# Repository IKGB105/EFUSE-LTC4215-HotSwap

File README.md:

# Hot-Swap eFuse (LTC4215)

12 V hot-swap / electronic-fuse front-end built around the LTC4215 hot-swap controller, documented as an
honest engineering logbook: every result is marked as calculated, simulated, or pending — no invented
placeholders. A deliberately small, fast project in the same series as
[LM317-Adjustable-PowerSupply](https://github.com/IKGB105/LM317-Adjustable-PowerSupply) and the LM2596/VRM
projects — chosen to add a self-contained portfolio result without derailing the in-progress 2-phase VRM
work, while staying on-theme for a server/GPU power-delivery specialization (live board insertion, inrush
limiting, and electronic circuit breaking).

- **Input:** 12 V DC
- **Circuit breaker trip:** 5 A (fast, non-resettable — latches off, no auto-retry)
- **Steady-state current limit (electrical):** 15 A (post-startup foldback release)
- **UV/OV lockout:** ~10.6 V / ~14.3 V (auto-retry on both)

> ⚠️ **15 A continuous is not thermally safe in still air on this layout.** A coupled electrical-thermal
> COMSOL model (current flow in the copper solved together with the heat) found the copper pours
> themselves dissipate 1.6 W — as much as every component combined — pushing the sense resistor (R5) to
> 170 °C and the MOSFET junction to its 150 °C limit at 15 A with convection only. **12.5 A continuous is
> comfortable** (128 °C / 113 °C). See [Thermal FEM](#thermal-fem-comsol) below.

> ⚠️ **Simulation + PCB layout only, not built.** Confirmed as the project scope from the start (same as
> `VRM_2PHASE_LTC1929`). The schematic and PCB are complete and ERC/DRC-clean but have not been sent to
> fabrication.

<table>
<tr>
<td><br><sub>KiCad — schematic</sub></td>
<td><br><sub>KiCad — PCB 3D render</sub></td>
<td><br><sub>COMSOL — thermal result (12 V, 15 A, R5/Q1 close-up)</sub></td>
</tr>
</table>

## Key results (simulated, verified from the LTspice `.raw` file)

- **Controlled startup:** inrush current peaks at **5.2 A**, landing almost exactly on the calculated 5 A
  circuit-breaker target — confirms the soft-start (SS) ramp and $R_{SENSE}$ are sized consistently with
  the breaker threshold. $V_{OUT}$ reaches 12 V in ≈51 ms.
- **Automatic UV recovery:** a 12 V → 8 V dip triggers a fast (~300 µs) output sag (the MOSFET's body
  diode conducting, not active protection), then a full, unattended recovery — but only ~106–112 ms after
  $V_{DD}$ returns, because the LTC4215's internal startup-sequencer delay re-arms on every restart, not
  just the first power-up.
- **Permanent latch-off on a hard short:** the circuit breaker trips within the datasheet's 20 µs filter
  and the output stays at 0 V for the rest of the run — no auto-retry, by design (`ocautoretry=0`).

Two non-obvious simulation pitfalls (a flat-DC source masking the entire power-up transient, and the
100 ms internal startup delay looking like a dead circuit) are documented in the report so they aren't
re-discovered from scratch on a future project using this IC family.

## Repository structure

```
docs/         LaTeX report (efuse_ltc4215.tex) + the LTC4215 datasheet
kicad/        KiCad project — schematic + PCB, ERC/DRC clean
simulation/   LTspice schematic (EFuse.asc) — startup, UV auto-retry, and OC fault tests
fem/          COMSOL thermal FEM — script-generated model, results CSVs, figures
```

## Document

The full report (controller selection, datasheet review, component derivations, LTspice simulation
methodology and results, PCB layout decisions, debugging pitfalls found along the way) is in
[`docs/efuse_ltc4215.pdf`](docs/efuse_ltc4215.pdf) — compiled and committed. Source is
[`docs/efuse_ltc4215.tex`](docs/efuse_ltc4215.tex) if you want to edit or recompile it yourself
(`pdflatex`).

## Design

Topology and component values are adapted directly from the LTC4215 datasheet's own validated reference
circuit ("12V Application with 5A Circuit Breaker," Figure 1) — every UV/OV/FB threshold is independently
re-derived and numerically cross-checked against the datasheet's comparator thresholds, not copied
blindly. Full derivation, equations, and a discussion of the one component substitution needed for
simulation (TVS: BZX84C15L in place of the real BOM's P6KE16A, no local SPICE model for the latter) are in
the report.

## SPICE Simulation (LTspice)

In [`simulation/`](simulation/) — three scenarios validated against the `.raw` file: controlled startup
(soft-start ramp, inrush current), an undervoltage fault with automatic recovery, and a hard output short
with permanent latch-off. See the report for full waveform data and the two IC-specific debugging
pitfalls found along the way.

## PCB (KiCad)

In [`kicad/EFUSE/`](kicad/EFUSE/) — ERC and DRC both clean. Two-layer board (single ground domain, 15 A
doesn't justify more layers). Notable layout decisions, documented in full in the report:

- QFN-24 package required (not the smaller SSOP-16) because this design uses the OV protection pin, which
  the SSOP-16 doesn't expose.
- Kelvin connection at the current-sense resistor ($R_{SENSE}$, 2512 package): SENSE− routed as a
  dedicated low-current tap directly off the sense resistor's own pad, not off the high-current trace
  toward the MOSFET.
- Dedicated +12 V and SOURCE/$V_{OUT}$ copper pours (not just traces), sized for the 15 A steady-state
  current per IPC-2221; solid GND pour on the bottom layer with via-stitching (not via-in-pad, to avoid a
  solder-wicking risk) under the IC's exposed pad.
- All-SMD assembly except where physically impossible: the TVS (DO-15, no SMD option at 600 W peak pulse
  power), the 12 mF output capacitor (no ceramic SMD exists at that value), and the input/output
  connectors (AMASS XT60).

## Thermal FEM (COMSOL)

In [`fem/`](fem/) — *Heat Transfer in Solids*, natural convection, 25 °C ambient, no heatsink, at the
continuous 12 V/15 A operating point. Unlike the LM317/LM2596 projects, the current flow through the
copper pours is solved together with the heat (an *Electric Currents, Shell* model coupled both ways to
the thermal one), not neglected — this is what surfaced the 1.6 W of copper $I^2R$ loss that the earlier
hand estimate (≈0.9 W) missed by almost 2×. The whole model is built from a script
([`fem/codigo/termico_efuse.py`](fem/codigo/termico_efuse.py)) that reads vias directly from the
`.kicad_pcb`, so it regenerates if the board changes.

**Key findings:**
- The sense resistor (R5), not the MOSFET, is the hottest part — same pattern as the LM2596 project, where
  the catch diode (not the regulator IC) turned out to be the real limit.
- Thermal vias added under R5/Q1 (stitched to a dedicated SENSE− copper island cut out of the ground pour
  — they can't go straight to GND without shorting) lower both by ≈10 °C, but the bigger issue is the total
  heat on a small board, not just how it escapes R5/Q1.
- 15 A continuous: R5 at 170 °C, Q1's junction at its 150 °C rated limit (convection only). With radiation
  (realistic for a solder-masked board): 112–124 °C on Q1, 133–141 °C on R5 — within limits but little
  margin.
- To reach 15 A continuous safely: 2 oz copper (halves the pour loss), wider/shorter pours, a
  higher-rated metal-strip R5, or airflow — documented as pending, not implemented.

## License

MIT — see [LICENSE](LICENSE).

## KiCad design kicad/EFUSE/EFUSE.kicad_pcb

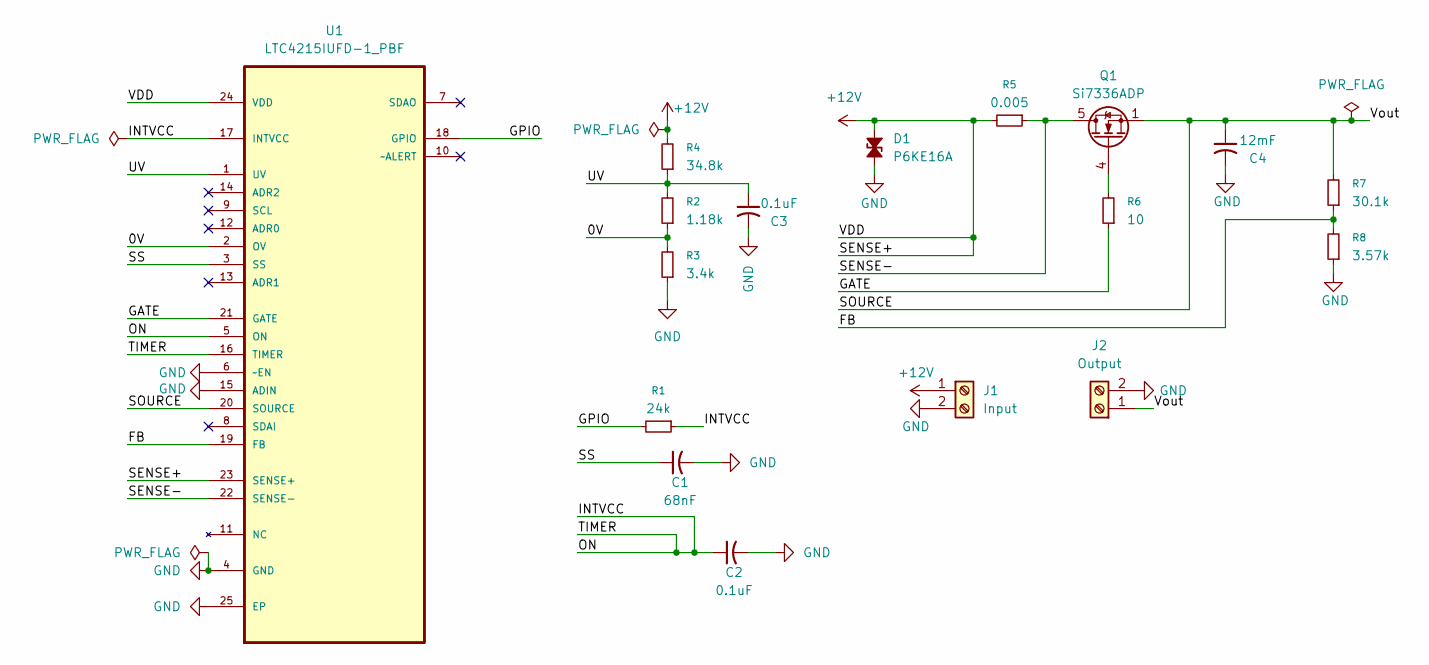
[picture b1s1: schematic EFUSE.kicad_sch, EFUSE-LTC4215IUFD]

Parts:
C1: 68nF; C_0805_2012Metric
C2, C3: 0.1uF; C_0805_2012Metric
C4: 12mF; CP_Radial_D16.0mm_P7.50mm
D1: P6KE16A; D_DO-15_P10.16mm_Horizontal
J1: Input; AMASS_XT60-M_1x02_P7.20mm_Vertical
J2: Output; AMASS_XT60-M_1x02_P7.20mm_Vertical
Q1: Si7336ADP; PowerPAK_SO-8_Single
R1: 24k; R_0805_2012Metric
R2: 1.18k; R_0805_2012Metric
R3: 3.4k; R_0805_2012Metric
R4: 34.8k; R_0805_2012Metric
R5: 0.005; R_2512_6332Metric
R6: 10; R_0805_2012Metric
R7: 30.1k; R_0805_2012Metric
R8: 3.57k; R_0805_2012Metric
U1: LTC4215IUFD-1_PBF; QFN50P400X500X80-25N; MPN LTC4215IUFD-2#TRPBF; DigiKey_Part_Number LTC4215IUFD-1#PBF-ND

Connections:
+12V: D1.1 (A1), J1.1, R4.2, R5.2, U1.23 (SENSE+), U1.24 (VDD)
/0V: R2.1, R3.2, U1.2 (OV)
/FB: R7.1, R8.2, U1.19 (FB)
/GATE: R6.1, U1.21 (GATE)
/GPIO: R1.2, U1.18 (GPIO)
/INTVCC: C2.1, R1.1, U1.5 (ON), U1.16 (TIMER), U1.17 (INTVCC)
/SENSE-: Q1.5 (D), R5.1, U1.22 (SENSE-)
/SOURCE: C4.1, J2.1, Q1.1 (S), Q1.2 (S), Q1.3 (S), R7.2, U1.20 (SOURCE)
/SS: C1.1, U1.3 (SS)
/UV: C3.1, R2.2, R4.1, U1.1 (UV)
GND: C1.2, C2.2, C3.2, C4.2, D1.2 (A2), J1.2, J2.2, R3.1, R8.1, U1.4 (GND), U1.6 (~EN), U1.15 (ADIN), U1.25 (EP)
unnamed: Q1.4 (G), R6.2

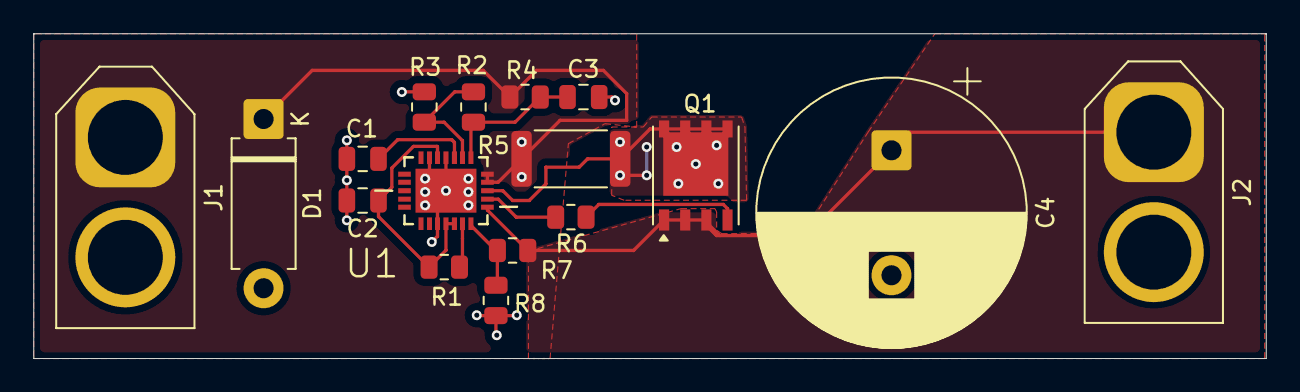
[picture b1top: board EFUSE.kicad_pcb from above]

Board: 2 copper layers, 74.0 x 19.5 mm, 17 parts (0 on the bottom side), 12 nets.
